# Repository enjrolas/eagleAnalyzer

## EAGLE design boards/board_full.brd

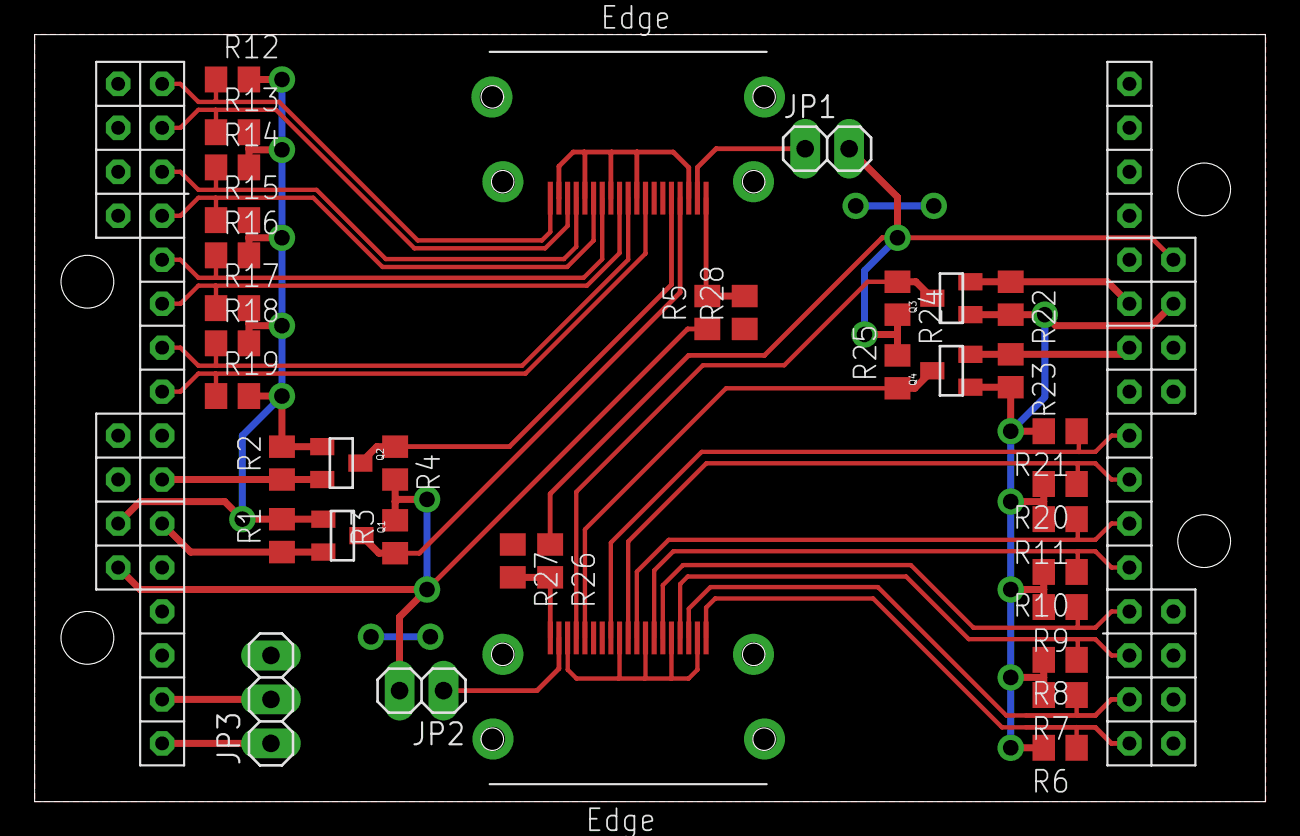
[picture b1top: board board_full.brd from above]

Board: 2 copper layers, 71.1 x 44.3 mm, 38 parts (0 on the bottom side), 35 nets.

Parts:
JP1, JP2: 1X02
JP3: 1X03
Q1, Q2, Q3, Q4: MOSFET-NCHANNELBSS138; SOT23
R1, R2, R3, R4, R5, R6, R7, R8, R9, R10, R11, R12, R13, R14, R15, R16, R17, R18, R19, R20, R21, R22, R23, R24, R25, R26, R27, R28: R0805
U$2, U$3: HDMI-TYPE-A-RECEPTICALFCI10029449; FCI-HDMI-TYPE-A-RECEPT
U$4: PAPILIO48

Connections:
3V3: Q1.1, Q2.1, R1.2, R2.2, R12.2, R13.2, R14.2, R15.2, R16.2, R17.2, R18.2, R19.2, U$4.CU_3V3
3V3A: Q3.1, Q4.1, R6.2, R7.2, R8.2, R9.2, R10.2, R11.2, R20.2, R21.2, R22.2, R23.2, U$4.AU_3V3
5V: JP2.2, R3.2, R4.2, R5.1, U$4.CU_5V
5VA: JP1.2, R24.2, R25.2, R26.1, U$4.AU_5V
DDC_SCL_RX: Q2.2, R2.1, U$4.C9
DDC_SCL_TX: Q4.2, R23.1, U$4.A09
DDC_SDA_RX: Q1.2, R1.1, U$4.C10
DDC_SDA_TX: Q3.2, R22.1, U$4.A10
GND: JP3.3, R27.1, R28.1, U$2.P$2, U$2.P$5, U$2.P$8, U$2.P$11, U$2.P$17, U$3.P$2, U$3.P$5, U$3.P$8, U$3.P$11, U$3.P$17, U$4.AL_GND, U$4.AU_GND, U$4.CL_GND, U$4.CU_GND
unnamed: JP3.2, U$4.C14
unnamed: JP3.1, U$4.C15
RX_DDC_SCL: Q2.3, R4.1, U$2.P$15
RX_DDC_SDA: Q1.3, R3.1, U$2.P$16
RX_HDMI_5V: JP1.1, U$2.P$18
RX_HPD: R5.2, R28.2, U$2.P$19
RX_TMDS0_N: R17.1, U$2.P$9, U$4.C5
RX_TMDS0_P: R16.1, U$2.P$7, U$4.C4
RX_TMDS1_N: R15.1, U$2.P$6, U$4.C3
RX_TMDS1_P: R14.1, U$2.P$4, U$4.C2
RX_TMDS2_N: R13.1, U$2.P$3, U$4.C1
RX_TMDS2_P: R12.1, U$2.P$1, U$4.C0
RX_TMDSC_N: R19.1, U$2.P$12, U$4.C7
RX_TMDSC_P: R18.1, U$2.P$10, U$4.C6
TX_DDC_SCL: Q4.3, R25.1, U$3.P$15
TX_DDC_SDA: Q3.3, R24.1, U$3.P$16
TX_HDMI_5V: JP2.1, U$3.P$18
TX_HPD: R26.2, R27.2, U$3.P$19
TX_TMDS0_N: R11.1, U$3.P$9, U$4.A5
TX_TMDS0_P: R10.1, U$3.P$7, U$4.A4
TX_TMDS1_N: R9.1, U$3.P$6, U$4.A3
TX_TMDS1_P: R8.1, U$3.P$4, U$4.A2
TX_TMDS2_N: R7.1, U$3.P$3, U$4.A1
TX_TMDS2_P: R6.1, U$3.P$1, U$4.A0
TX_TMDSC_N: R21.1, U$3.P$12, U$4.A7
TX_TMDSC_P: R20.1, U$3.P$10, U$4.A6

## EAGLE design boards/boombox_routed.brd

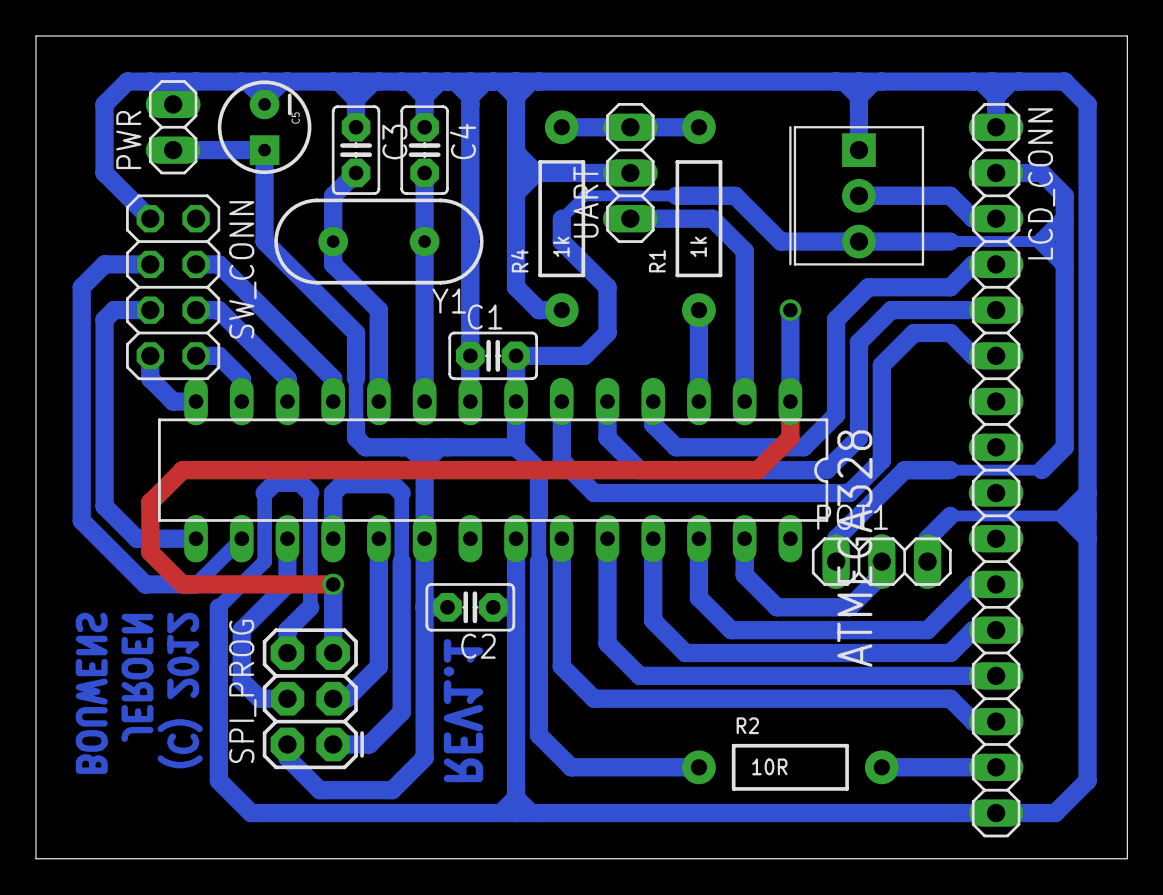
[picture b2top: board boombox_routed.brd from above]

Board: 2 copper layers, 60.6 x 45.7 mm, 17 parts (0 on the bottom side), 27 nets.

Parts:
ATMEGA328: MEGA8-P; DIL28-3
C1, C2: 0.1uF; C2.5-2
C3, C4: 22pF; C2.5-2
C5: 10uF; CPOL-RADIAL-10UF-25V
CONTR: 10k; 3362U
LCD_CONN: 1X16
POT1: 1k; 1X03
PWR: 1X02
R1, R4: 1k; AXIAL-0.4
R2: 10R; AXIAL-0.4
SPI_PROG: AVR_SPI_PRG_6PTH; 2X3
SW_CONN: 2X04
UART: 1X03
Y1: 16 MHz; HC49US

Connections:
GND: ATMEGA328.8, ATMEGA328.22, C1.1, C2.1, C3.1, C4.1, C5.2, CONTR.P$1, LCD_CONN.1, LCD_CONN.16, POT1.3, PWR.2, R4.P$1, SPI_PROG.6, SW_CONN.1, UART.2
unnamed: ATMEGA328.10, C3.2, Y1.2
unnamed: ATMEGA328.9, C4.2, Y1.1
unnamed: CONTR.P$2, LCD_CONN.3
unnamed: ATMEGA328.3, R1.P$1
unnamed: R1.P$2, R4.P$2, UART.3
unnamed: ATMEGA328.2, UART.1
unnamed: ATMEGA328.4, LCD_CONN.4
unnamed: ATMEGA328.5, LCD_CONN.5
unnamed: ATMEGA328.6, LCD_CONN.6
unnamed: LCD_CONN.15, R2.P$2
unnamed: ATMEGA328.23, LCD_CONN.14
unnamed: ATMEGA328.24, LCD_CONN.13
unnamed: ATMEGA328.25, LCD_CONN.12
unnamed: ATMEGA328.26, LCD_CONN.11
unnamed: ATMEGA328.19, SPI_PROG.3
unnamed: ATMEGA328.18, SPI_PROG.1
unnamed: ATMEGA328.17, SPI_PROG.4
unnamed: ATMEGA328.14, SW_CONN.7
unnamed: ATMEGA328.27, POT1.2
unnamed: ATMEGA328.15, SW_CONN.5
unnamed: ATMEGA328.12, SW_CONN.6
unnamed: ATMEGA328.13, SW_CONN.8
unnamed: ATMEGA328.11, SW_CONN.4
unnamed: ATMEGA328.16, SW_CONN.3
unnamed: ATMEGA328.1, SPI_PROG.5
VCC: ATMEGA328.7, ATMEGA328.20, C1.2, C2.2, C5.1, CONTR.P$3, LCD_CONN.2, POT1.1, PWR.1, R2.P$1, SPI_PROG.2

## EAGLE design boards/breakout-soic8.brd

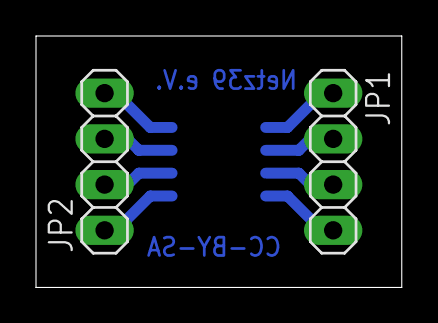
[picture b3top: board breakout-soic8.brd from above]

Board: 2 copper layers, 20.3 x 14.0 mm, 3 parts (1 on the bottom side), 8 nets.

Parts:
IC2: NE555D; SO08
JP1, JP2: 1X04

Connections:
unnamed: IC2.1, JP2.1
unnamed: IC2.2, JP2.2
unnamed: IC2.3, JP2.3
unnamed: IC2.4, JP2.4
unnamed: IC2.5, JP1.1
unnamed: IC2.6, JP1.2
unnamed: IC2.7, JP1.3
unnamed: IC2.8, JP1.4

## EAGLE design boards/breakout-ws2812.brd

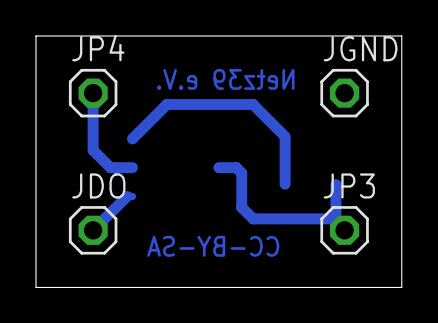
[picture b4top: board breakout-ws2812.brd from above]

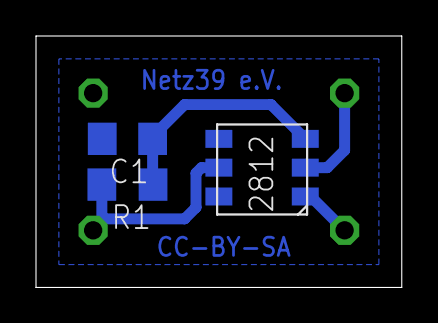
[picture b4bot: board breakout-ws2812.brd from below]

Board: 2 copper layers, 20.3 x 14.0 mm, 7 parts (3 on the bottom side), 5 nets.

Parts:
C1: C1206
JDO: DO; 1X01
JGND: GND; 1X01
JP3: VDD; 1X01
JP4: DI; 1X01
R1: R1206
U$1: WS2812

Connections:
GND: C1.2, JGND.1, U$1.6
JDD: JP3.1, R1.2, U$1.5
JDI: JP4.1, U$1.2
unnamed: JDO.1, U$1.1
unnamed: C1.1, R1.1, U$1.3

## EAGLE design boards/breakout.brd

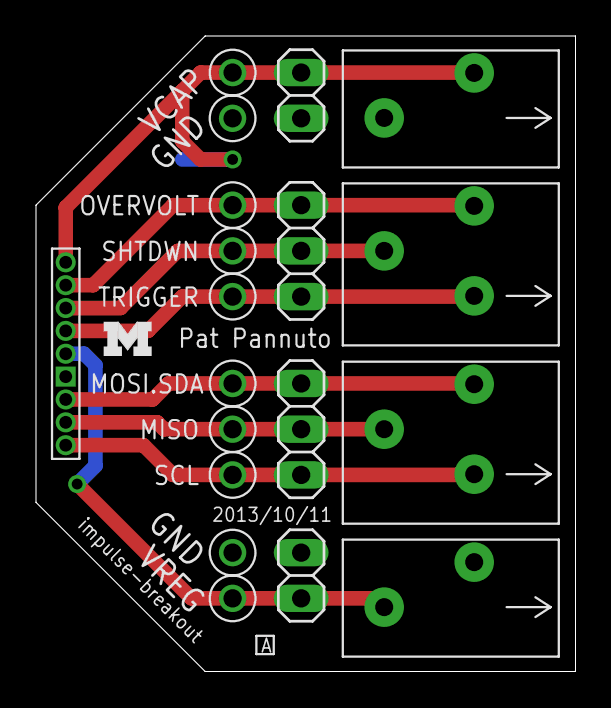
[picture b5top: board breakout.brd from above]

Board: 2 copper layers, 30.0 x 35.3 mm, 20 parts (0 on the bottom side), 9 nets.

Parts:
J3: IMPULSE_GECKO_HEADER; HEADER1X9/0.05IN
J4, J5: SPRING-TERMINAL_3/PTSA-ZZ_2.5MM; 1X3/PTSA-ZZ_2.5MM
J6, J7: SPRING-TERMINAL_2/PTSA-ZZ_2.5MM; 1X2/PTSA-ZZ_2.5MM
JP1, JP2: 1X03
JP3, JP4: 1X02
TP1, TP2, TP3, TP4, TP5, TP6, TP7, TP8, TP9, TP10: TEST_POINT_0.040IN; TESTPOINT_0.040IN
U$1: UMICH_SOLID_SMALL; UMICH_SOLID_75MIL

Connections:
GND: J3.0, J6.1, J7.2, JP3.1, JP4.2, TP8.TESTPOINT, TP9.TESTPOINT
MISO0: J3.-2, J5.2, JP2.2, TP5.TESTPOINT
MOSI0: J3.-1, J5.3, JP2.3, TP4.TESTPOINT
OV: J3.4, J4.3, JP1.3, TP1.TESTPOINT
SCLK0: J3.-3, J5.1, JP2.1, TP6.TESTPOINT
SHD: J3.3, J4.2, JP1.2, TP2.TESTPOINT
TRIG: J3.2, J4.1, JP1.1, TP3.TESTPOINT
VCAP: J3.5, J6.2, JP3.2, TP7.TESTPOINT
VCC: J3.1, J7.1, JP4.1, TP10.TESTPOINT

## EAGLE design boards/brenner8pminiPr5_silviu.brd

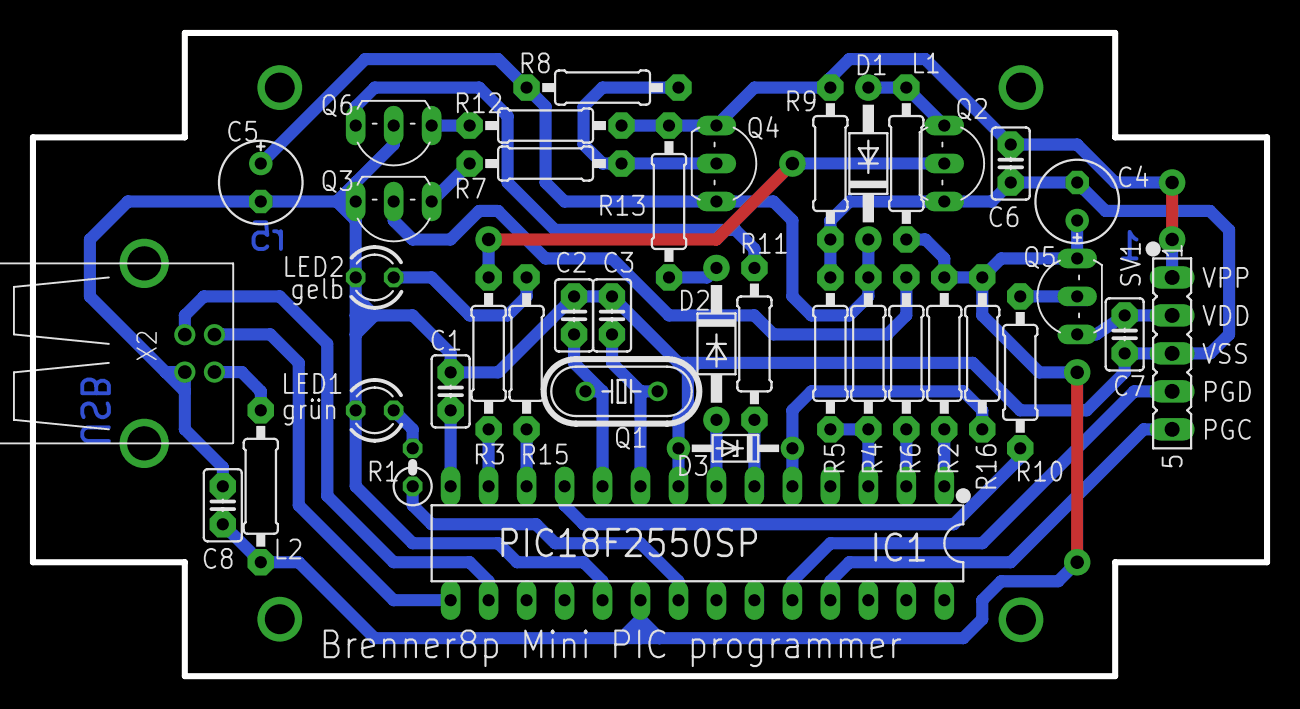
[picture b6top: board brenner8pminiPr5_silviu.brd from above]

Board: 2 copper layers, 82.5 x 43.0 mm, 39 parts (0 on the bottom side), 34 nets.

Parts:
C1: 220nF; C025-025X050
C2, C3: 22p; C025-025X050
C4: 10µF; E2,5-6E
C5: 47µF; E2,5-6E
C6: 1nF; C025-025X050
C7, C8: 100nF; C025-025X050
D1, D2: BAT43; DO41-10
D3: 3,3V; DO34Z7
IC1: PIC18F2550SP; DIL28-3
L1: 680µH; 0207/10
L2: 10µH; 0207/10
LED1: grün; LED3MM
LED2: gelb; LED3MM
Q1: 20 MHz; HC49/S
Q2, Q3: BC338-25; TO92-EBC
Q4, Q5: BC328-25; TO92-EBC
Q6: BF959; TO92-BEC
R1: 1k; 0207/2V
R2: 10 k; 0207/10
R3, R6, R7, R9, R10, R11: 10k; 0207/10
R4: 4k7; 0207/10
R5: 2k2; 0207/10
R8: 100k; 0207/10
R12, R13: 100; 0207/10
R15: 1 k; 0207/10
R16: 330; 0207/10
SV1: ICSP; FE05-1
X2: USB-B-H

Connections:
+12V: C5.+, D1.C, Q4.E, R4.2, R8.2
CLOCK_18: IC1.25, SV1.5
DATA_18: IC1.24, SV1.4
unnamed: IC1.15, X2.D-
unnamed: IC1.16, X2.D+
unnamed: L2.1, X2.VBUS
unnamed: LED1.A, R1.2
unnamed: C1.1, IC1.14
unnamed: C2.1, IC1.10, Q1.1
unnamed: C3.1, IC1.9, Q1.2
unnamed: IC1.1, R2.1
unnamed: Q5.B, R10.2
unnamed: IC1.12, R15.2
unnamed: IC1.11, R10.1
unnamed: LED2.A, R15.1
unnamed: D1.A, L1.2, Q2.C
unnamed: Q2.B, R3.1
unnamed: IC1.13, R3.2
unnamed: IC1.21, R1.1
unnamed: C7.1, Q5.C, SV1.2
unnamed: IC1.3, R4.1, R5.2
unnamed: Q6.B, R11.2
unnamed: IC1.6, R11.1
unnamed: Q3.B, R6.1
unnamed: Q6.C, R12.1
unnamed: Q3.C, R7.1
unnamed: Q4.B, R7.2, R8.1
unnamed: D2.A, IC1.7
unnamed: D2.C, R13.1
unnamed: IC1.2, R6.2
UREF: D3.C, IC1.5, R16.1
VDD: C4.+, C8.1, IC1.20, L1.1, L2.2, Q5.E, R2.2, R16.2
VPP_8_14_18: C6.1, Q4.C, R9.2, R12.2, R13.2, SV1.1
VSS: C1.2, C2.2, C3.2, C4.-, C5.-, C6.2, C7.2, C8.2, D3.A, IC1.8, IC1.19, LED1.K, LED2.K, Q2.E, Q3.E, Q6.E, R5.1, R9.1, SV1.3, X2.GND

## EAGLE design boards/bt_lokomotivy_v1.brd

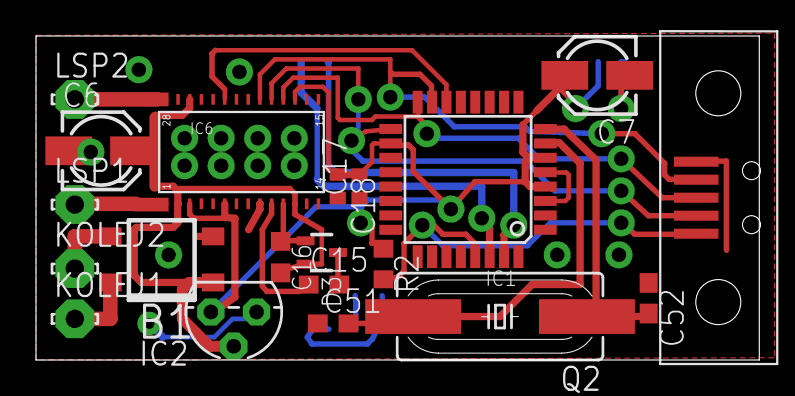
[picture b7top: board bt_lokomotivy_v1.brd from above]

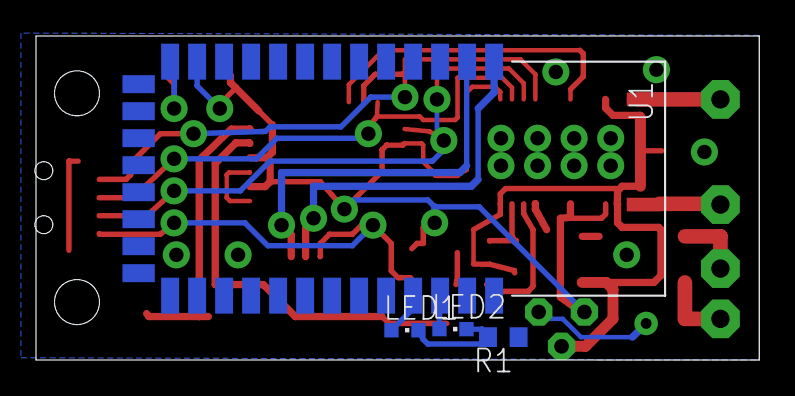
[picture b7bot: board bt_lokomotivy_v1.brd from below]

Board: 2 copper layers, 40.2 x 18.0 mm, 24 parts (4 on the bottom side), 22 nets.

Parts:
B1: RECTIFIER-S80; TO-269AA
C6, C7: 10u; 153CLV-0405
C15: 10n; C0603
C16: 220n; C0603K
C17, C18: 100n; C0402
C51, C52: 20pF; C0603
D3: SOT323
IC1: MEGA8-AI; TQFP32-08
IC2: HT7533-1 TO92; TO92
IC6: L6470; HTSSOP28
KOLEJ1, KOLEJ2: LSP10
LED1, LED2: CHIPLED_0603
LSP1, LSP2: LSP10
Q2: 16MHz; HC49UP
R1: R0603
R2: 4k7; R0603
U1: HC_05; BLUETOOTH_SMD
U$2: SEI-5

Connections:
3V3: C7.+, C17.2, C18.1, IC1.4, IC1.6, IC1.18, IC2.3, IC6.3, IC6.6, IC6.17, R2.1, U1.12
CS: IC1.14, IC6.23
GND: B1.-, C6.-, C7.-, C17.1, C18.2, C51.1, C52.1, IC1.3, IC1.5, IC1.21, IC2.1, IC6.9, IC6.13, IC6.21, IC6.27, R1.1, U1.13, U$2.P$1
MISO: IC1.16, IC6.18, U$2.P$3
MOSI: IC1.15, IC6.20, U$2.P$2
unnamed: IC1.30, U1.1
unnamed: LED1.C, LED2.C, R1.2
unnamed: B1.AC1, KOLEJ1.MP
unnamed: B1.AC2, KOLEJ2.MP
unnamed: IC1.31, U1.2
unnamed: IC1.29, R2.2, U$2.P$5
unnamed: C51.2, IC1.7, Q2.2
unnamed: C52.2, IC1.8, Q2.1
unnamed: LED1.A, U1.31
unnamed: LED2.A, U1.32
unnamed: C15.1, IC6.10
unnamed: C15.2, D3.1
SCK: IC1.17, IC6.19, U$2.P$4
VBOOTX: C16.1, D3.2, IC6.11
VIN: B1.+, C6.+, C16.2, D3.3, IC2.2, IC6.2, IC6.12, IC6.16, IC6.26
X1: IC6.1, LSP1.MP
X2: IC6.28, LSP2.MP

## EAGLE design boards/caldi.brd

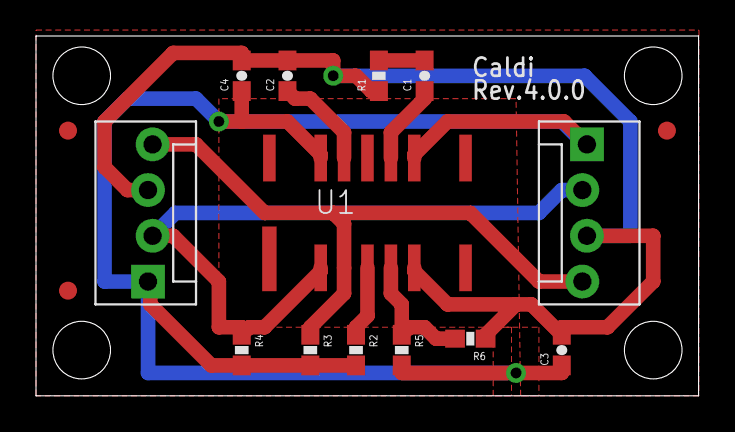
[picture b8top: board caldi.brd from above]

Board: 2 copper layers, 36.8 x 20.0 mm, 17 parts (1 on the bottom side), 9 nets.

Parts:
C1: 1uF; 0603-CAP
C2: 1.5uF; 0603-CAP
C3, C4: 10uF; 0603-CAP
JP1, JP2: MOLEX-1X4_LOCK
JP3, JP4, JP5: FIDUCIAL1X2; FIDUCIAL-1X2
R1: 20; 0603-RES
R2, R3, R4, R5: 10K; 0603-RES
R6: 0; 0603-RES
U1: AMG885X
U$4: PA_LOGO_SYMMED; PA_LOGO_AGENT_MED_SYM

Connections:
5V: C3.1, C4.1, JP1.1, JP2.1, R2.2, R3.2, R4.2, R5.2, U1.9, U1.13
!INT!: R2.1, U1.4
ADSEL: R5.1, R6.2, U1.5
GND: C2.2, C3.2, C4.2, JP1.3, JP2.3, R1.1, R6.1, U1.6
unnamed: C1.1, U1.10
unnamed: C1.2, R1.2
unnamed: C2.1, U1.12
SCL: JP1.4, JP2.4, R3.1, U1.3
SDA: JP1.2, JP2.2, R4.1, U1.2

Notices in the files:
boards/boombox_routed.brd:
(C) 2012
boards/breakout-soic8.brd:
CC-BY-SA
parts and their libraries:
SparkFun-DiscreteSemi: Licensing: CC v3.0 Share-Alike You are welcome to use this library for commercial purposes.
PatternAgents-Logos: License : http://creativecommons.org/licenses/by-sa/3.0
(Creative Commons 3.0)
